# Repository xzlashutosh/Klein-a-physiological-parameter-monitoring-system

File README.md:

# Klein
It is a fully functional prototype of a physiological parameter monitoring system. It is a device that monitors and displays body temperature, heart rate, blood oxygen, and ECG on demand. Apart from it, the current date, day, month, local time are also displayed. 

Have a look at the video of the first prototype here - 
https://youtu.be/E1iHC5x9eKE

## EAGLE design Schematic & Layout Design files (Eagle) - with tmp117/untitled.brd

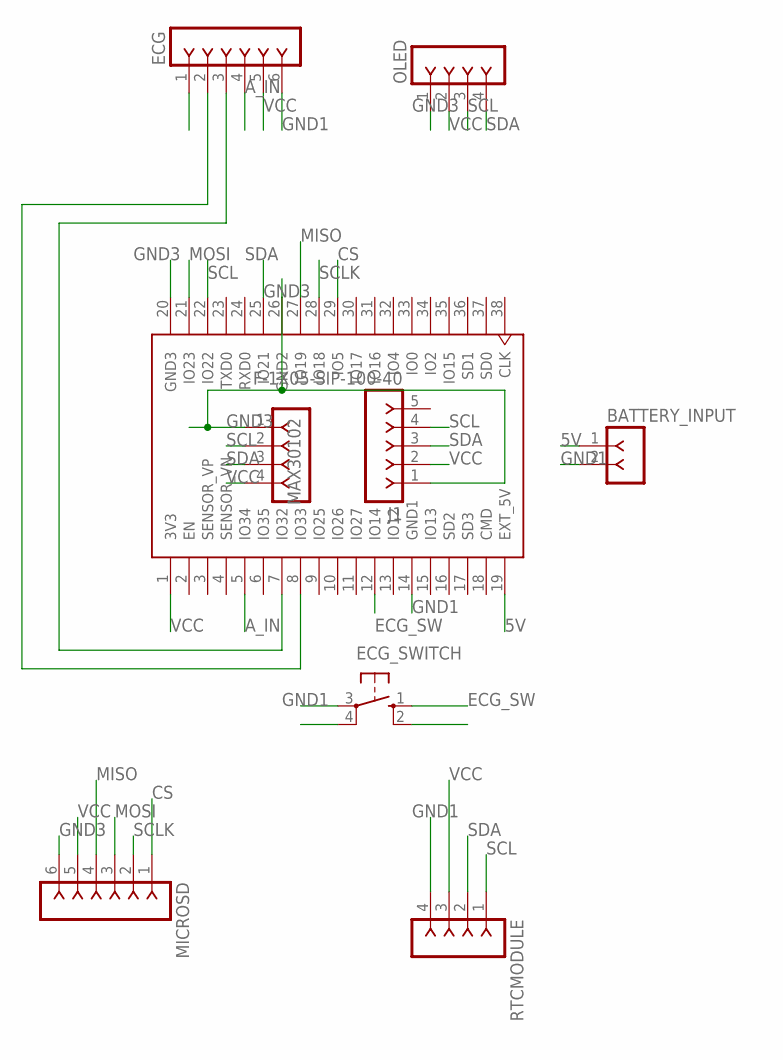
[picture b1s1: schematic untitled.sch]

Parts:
BATTERY_INPUT: F-1X02-SIP-100-40; SIP-100-02-40
ECG: F-1X06-SIP-100-40; SIP-100-06-40
ECG_SWITCH: 10-XX; B3F-10XX
J1: F-1X05-SIP-100-40; SIP-100-05-40
MAX30102: F-1X04-SIP-100-40; SIP-100-04-40
MICROSD: F-1X06-SIP-100-40; SIP-100-06-40
OLED: F-1X04-SIP-100-40; SIP-100-04-40
RTCMODULE: F-1X04-SIP-100-40; SIP-100-04-40
U1: ESP32-DEVKITC-32D; MODULE_ESP32-DEVKITC-32D

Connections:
5V: BATTERY_INPUT.1, U1.19 (EXT_5V)
A_IN: ECG.4, U1.5 (IO34)
CS: MICROSD.1, U1.29 (IO5)
ECG_SW: ECG_SWITCH.1 (S), U1.12 (IO14)
GND1: BATTERY_INPUT.2, ECG.6, ECG_SWITCH.3, RTCMODULE.4, U1.14 (GND1)
GND3: J1.1, MAX30102.1, MICROSD.6, OLED.1, U1.20 (GND3), U1.26 (GND2)
MISO: MICROSD.4, U1.27 (IO19)
MOSI: MICROSD.3, U1.21 (IO23)
unnamed: ECG.2, U1.8 (IO33)
unnamed: ECG.3, U1.7 (IO32)
SCL: J1.4, MAX30102.2, OLED.3, RTCMODULE.1, U1.22 (IO22)
SCLK: MICROSD.2, U1.28 (IO18)
SDA: J1.3, MAX30102.3, OLED.4, RTCMODULE.2, U1.25 (IO21)
VCC: ECG.5, J1.2, MAX30102.4, MICROSD.5, OLED.2, RTCMODULE.3, U1.1 (3V3)

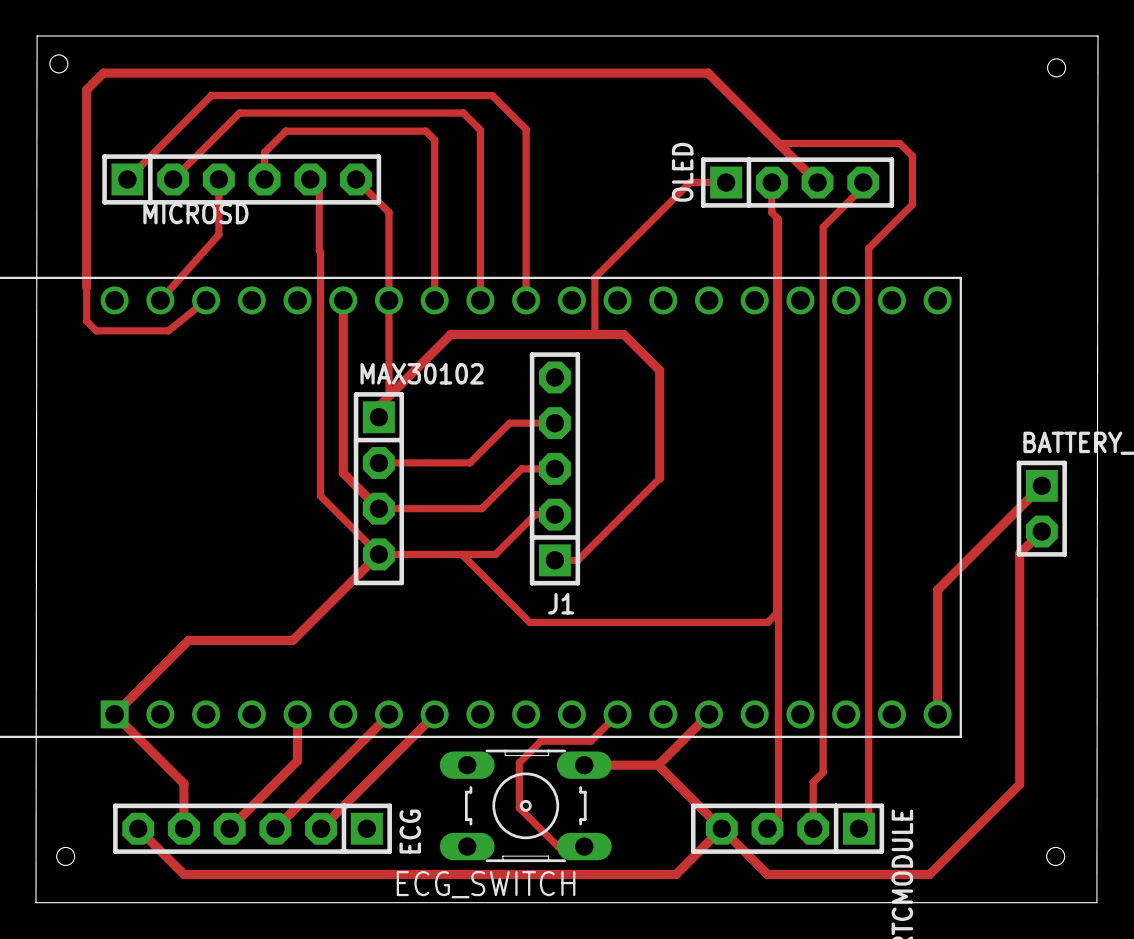
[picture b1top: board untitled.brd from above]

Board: 2 copper layers, 59.0 x 48.1 mm, 9 parts (0 on the bottom side), 14 nets.

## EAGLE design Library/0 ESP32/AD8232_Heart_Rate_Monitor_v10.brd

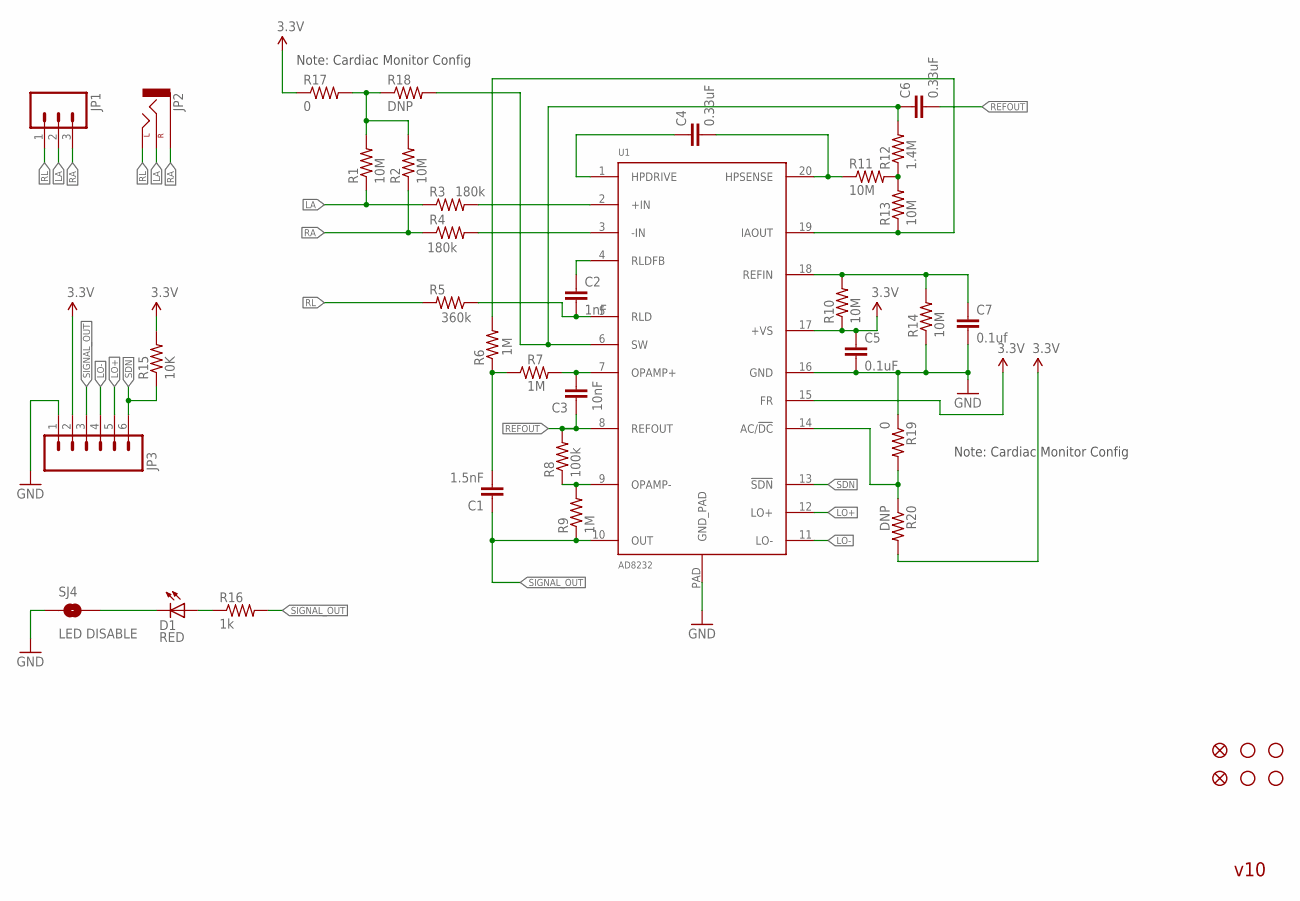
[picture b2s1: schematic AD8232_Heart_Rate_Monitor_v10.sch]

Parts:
C1: 1.5nF; 0603-CAP
C2: 1nF; 0603-CAP
C3: 10nF; 0603-CAP
C4, C6: 0.33uF; 0805
C5: 0.1uF; 0603-CAP
C7: 0.1uf; 0603-CAP
D1: RED; LED-0603
FID1, FID2: FIDUCIAL1X2; FIDUCIAL-1X2
JP1: M03PTH; 1X03
JP2: AUDIO-JACKSMD2; AUDIO-JACK-3.5MM-SMD
JP3: M06SIP; 1X06
R1, R2, R10, R11, R13, R14: 10M; 0603-RES
R3, R4: 180k; 0603-RES
R5: 360k; 0603-RES
R6, R7, R9: 1M; 0603-RES
R8: 100k; 0603-RES
R12: 1.4M; 0603-RES
R15: 10K; 0603-RES
R16: 1k; 0603-RES
R17, R19: 0; 0603
R18, R20: DNP; 0603
SJ4: LED DISABLE; SJ_2S-TRACE
STANDOFF1, STANDOFF2, STANDOFF3, STANDOFF4: STAND-OFF
U1: AD8232; LFCSP_20

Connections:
3.3V: C5.1, JP3.2, R10.1, R15.2, R17.1, R20.2, U1.15 (FR), U1.17 (+VS)
GND: C5.2, C7.2, JP3.1, R14.1, R19.1, SJ4.1, U1.16 (GND), U1.PAD (GND_PAD)
LA: JP1.2, JP2.RING (RIGHT), R1.1, R3.1
LO+: JP3.5, U1.12 (LO+)
LO-: JP3.4, U1.11 (LO-)
unnamed: R3.2, U1.2 (+IN)
unnamed: R4.2, U1.3 (-IN)
unnamed: C3.2, R7.2, U1.7 (OPAMP+)
unnamed: C4.2, R11.1, U1.20 (HPSENSE)
unnamed: C7.1, R10.2, R14.2, U1.18 (REFIN)
unnamed: D1.A, R16.1
unnamed: R8.1, R9.2, U1.9 (OPAMP-)
unnamed: R6.2, R13.1, U1.19 (IAOUT)
unnamed: C1.2, R6.1, R7.1
unnamed: D1.C, SJ4.2
unnamed: R19.2, R20.1, U1.14 (AC/!DC)
unnamed: C4.1, U1.1 (HPDRIVE)
unnamed: R11.2, R12.1, R13.2
unnamed: C6.1, R12.2, R18.2, U1.6 (SW)
unnamed: C2.1, U1.4 (RLDFB)
unnamed: C2.2, R5.1, U1.5 (RLD)
unnamed: R1.2, R2.2, R17.2, R18.1
RA: JP1.3, JP2.SLEEVE, R2.1, R4.1
REFOUT: C3.1, C6.2, R8.2, U1.8 (REFOUT)
RL: JP1.1, JP2.TIP (LEFT), R5.2
SDN: JP3.6, R15.1, U1.13 (!SDN)
SIGNAL_OUT: C1.1, JP3.3, R9.1, R16.2, U1.10 (OUT)

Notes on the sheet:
v10
Note: Cardiac Monitor Config

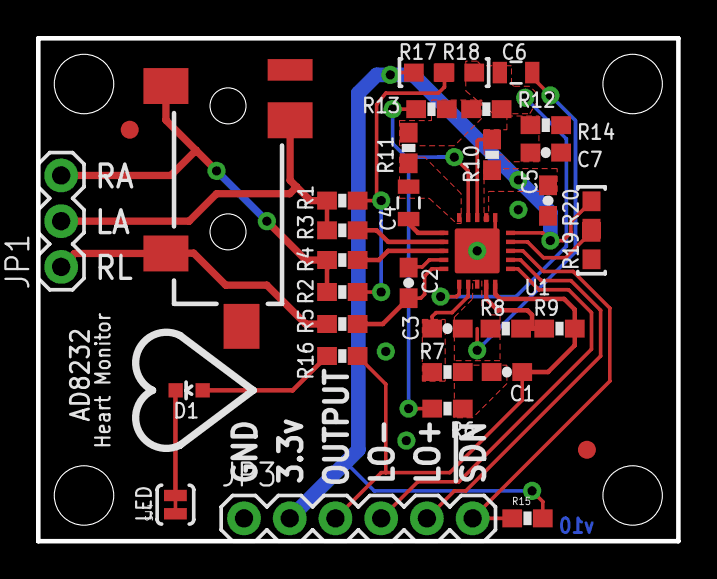
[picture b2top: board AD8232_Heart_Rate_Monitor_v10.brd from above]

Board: 2 copper layers, 35.6 x 27.9 mm, 39 parts (0 on the bottom side), 27 nets.

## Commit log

2021-05-07 Create Schematic and Layout in Eagle
2021-05-07 Create a
2021-05-07 folder rename

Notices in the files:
parts and their libraries:
con-headers-jp: Copyright (C) 2008, Bob Starr
SparkFun-Aesthetics: Licensing: CC v3.0 Share-Alike You are welcome to use this library for commercial purposes.
